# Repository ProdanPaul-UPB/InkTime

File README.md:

# InkTime — Open Source Smartwatch

InkTime is a low-power, open-source smartwatch built around the Nordic nRF52840 SoC and a 1.54" e-paper display. The goal was to design a device that can run for weeks on a single charge while still being useful as a daily wearable — no constant charging, no always-on backlight draining the battery.

This repo contains the full hardware design: schematic, PCB layout, manufacturing files, and the complete 3D assembly.

---

## Block Diagram

```
                        ┌─────────────────────────────────────────┐
                        │            nRF52840 (U1)                │
  USB-C (J4) ──► ESD ──►│ USB D+/D-          SPI ──────────────► │──► EPD Display (J1)
       │        (D3)    │                                         │    (Waveshare 1.54")
       │                │ I2C ──────────────────────────────────► │──► BMA423 IMU (IC3)
       ▼                │                   ├──────────────────► │──► MAX17048 Fuel Gauge (U3)
  BQ25180 (IC1) ───────►│ VBUS sense         └──────────────────► │──► DRV2605 Haptic (IC2)
  LiPo Charger          │                                         │
       │                │ GPIO ──────────────────────────────────►│──► SW_UP / SW_ENT / SW_DN
       ▼                │                                         │
  AKYGA LP502030        │ RF ────────────────────────────────────►│──► Matching Network
  3.7V / 250mAh         │                                         │    └──► ANT1 (2.4GHz)
       │                │ SWD ───────────────────────────────────►│──► TC2030-IDC (J2)
       ▼                └─────────────────────────────────────────┘
  RT6160A (IC9)
  DC-DC → 3.3V ──────────────────────────────────────────────────► All 3.3V rails
```

---

## Bill of Materials

| Ref | Component | Value / Part | Package | Datasheet | JLC Parts |
|-----|-----------|--------------|---------|-----------|-----------|
| U1 | Nordic nRF52840 | nRF52840-QIAA | QFN-73 | [Datasheet](https://infocenter.nordicsemi.com/pdf/nRF52840_PS_v1.7.pdf) | [JLC](https://jlcpcb.com/partdetail/NordicSemiconductor-nRF52840QIAA/C190794) |
| IC1 | TI BQ25180 | LiPo Charger | DSBGA-9 | [Datasheet](https://www.ti.com/lit/ds/symlink/bq25180.pdf) | [JLC](https://jlcpcb.com/parts/componentSearch?searchTxt=BQ25180) |
| IC9 | RT6160A | DC-DC Buck 3.3V | WSON-6 | [Datasheet](https://www.richtek.com/assets/product_file/RT6160A/DS6160A-00.pdf) | [JLC](https://jlcpcb.com/parts/componentSearch?searchTxt=RT6160A) |
| U3 | MAX17048G+T10 | Fuel Gauge | SOT-23-6 | [Datasheet](https://www.analog.com/media/en/technical-documentation/data-sheets/MAX17048-MAX17049.pdf) | [JLC](https://jlcpcb.com/parts/componentSearch?searchTxt=MAX17048) |
| IC3 | BMA423 | Accelerometer | LGA-12 | [Datasheet](https://www.bosch-sensortec.com/media/boschsensortec/downloads/datasheets/bst-bma423-ds000.pdf) | [JLC](https://jlcpcb.com/parts/componentSearch?searchTxt=BMA423) |
| IC2 | DRV2605YZFR | Haptic Driver | DSBGA-12 | [Datasheet](https://www.ti.com/lit/ds/symlink/drv2605.pdf) | [JLC](https://jlcpcb.com/parts/componentSearch?searchTxt=DRV2605) |
| D3 | USBLC6-2SC6Y | USB ESD | SOT-363 | [Datasheet](https://www.st.com/resource/en/datasheet/usblc6-2.pdf) | [JLC](https://jlcpcb.com/parts/componentSearch?searchTxt=USBLC6-2SC6Y) |
| J4 | KH-TYPE-C-16P | USB-C Receptacle | SMD | — | [JLC](https://jlcpcb.com/parts/componentSearch?searchTxt=TYPE-C-16P) |
| J1 | Molex 503480-2400 | 24-pin FPC | SMD | [Datasheet](https://www.molex.com/en-us/products/part-detail/503480-2400) | [JLC](https://jlcpcb.com/parts/componentSearch?searchTxt=503480-2400) |
| J2 | TC2030-IDC | SWD Connector | THT | [Datasheet](https://www.tag-connect.com/product/tc2030-idc-nl) | — |
| ANT1 | 2450AT18B100E | 2.4GHz Antenna | SMD | [Datasheet](https://www.johansontechnology.com/datasheets/2450AT18B100E/2450AT18B100E.pdf) | [JLC](https://jlcpcb.com/parts/componentSearch?searchTxt=2450AT18B100E) |
| X1 | 32MHz Crystal | HFXO | SMD | — | [JLC](https://jlcpcb.com/parts/componentSearch?searchTxt=32MHz+crystal) |
| X2 | 32.768kHz Crystal | LFXO | SMD | — | [JLC](https://jlcpcb.com/parts/componentSearch?searchTxt=32.768kHz+crystal) |
| SW1-3 | EVP-AKE31A | Tactile Button | SMD | [Datasheet](https://industrial.panasonic.com/cdbs/www-data/pdf/ATV0000/ATV0000CE5.pdf) | [JLC](https://jlcpcb.com/parts/componentSearch?searchTxt=EVP-AKE31A) |
| — | AKYGA LP502030 | 3.7V / 250mAh LiPo | — | [Datasheet](https://www.tme.eu/Document/b9e12bf26ad0ba929a22ab5d58f022cd/AKY0106.pdf) | External |
| — | Waveshare WSH-12561 | 1.54" EPD Display | FPC-24 | [Datasheet](https://www.tme.eu/Document/0ca57a8ffbcd57b5bca53252eb9d6ec3/WSH-12561.pdf) | External |
| — | DFRobot FIT0774 | Vibration Motor | Coin 10×2.7mm | [Product page](https://www.tme.eu/ro/details/df-fit0774/motoare-dc/dfrobot/fit0774/) | External |
| Q3 | DMG2305UX | P-MOSFET | SOT-523 | [Datasheet](https://www.diodes.com/assets/Datasheets/DMG2305UX.pdf) | [JLC](https://jlcpcb.com/parts/componentSearch?searchTxt=DMG2305UX) |
| Q4 | SI1308EDL | N-MOSFET | SC-70 | [Datasheet](https://www.vishay.com/docs/73217/si1308edl.pdf) | [JLC](https://jlcpcb.com/parts/componentSearch?searchTxt=SI1308EDL) |
| L5 | 68µH Inductor | EPD Boost | 0402 | — | [JLC](https://jlcpcb.com/parts/componentSearch?searchTxt=68uH+0402) |
| L1 | 3.9nH Inductor | RF Matching | 0402 | — | [JLC](https://jlcpcb.com/parts/componentSearch?searchTxt=3.9nH+0402) |
| L2 | 15nH Inductor | RF Matching | 0402 | — | [JLC](https://jlcpcb.com/parts/componentSearch?searchTxt=15nH+0402) |
| L7 | 4.7µH Inductor | DC-DC Switching | 0402 | — | [JLC](https://jlcpcb.com/parts/componentSearch?searchTxt=4.7uH+0402) |
| R9 | 10kΩ | TS/MR Pull-down | 0201 | — | [JLC](https://jlcpcb.com/parts/componentSearch?searchTxt=10k+0201) |
| Various C | 100nF / 1µF / 10µF / 22µF | Decoupling | 0201 / 0402 | — | [JLC](https://jlcpcb.com/parts/componentSearch?searchTxt=100nF+0201) |

---

## Hardware Description

### Power Path

Power enters through the USB-C connector (J4). The BQ25180 charger (IC1) handles incoming VBUS and takes care of charging the LiPo battery safely — it supports up to 1A charge current with I²C-configurable parameters. The RT6160A (IC9) is a synchronous buck DC-DC converter that takes the battery voltage (3.0–4.2V) and steps it down to a clean 3.3V rail used by everything else on the board. The MAX17048 fuel gauge (U3) sits on the I²C bus and reports state of charge to the MCU so the watch can display battery percentage without the MCU having to do any ADC math itself.

The battery (AKYGA LP502030) is soldered directly to two test pads on the board rather than using a JST connector — this saves ~2mm of vertical height which matters a lot inside a watch case.

### Microcontroller

The nRF52840 (U1) is the brain of the device. It's a Cortex-M4F running at 64MHz with built-in Bluetooth 5.0 and a hardware USB controller. We used the QFN-73 package which has a 5×5mm exposed thermal pad underneath — there are thermal vias going through to the bottom GND plane to help with heat dissipation. The chip runs off the 3.3V rail and has 13 decoupling capacitors placed in a ring around its pads, as close to the power pins as the 2.54mm grid allows.

### Display Interface

The 1.54" e-paper display (Waveshare WSH-12561) connects through a 24-pin FPC connector (J1, Molex 503480-2400) on the left edge of the board. The EPD uses a 4-wire SPI interface plus three control lines (DC, RST, BUSY). The display only draws current during refresh — in static mode it consumes essentially nothing, which is the main reason e-paper was chosen for a watch that's supposed to last weeks.

Driving an EPD requires specific voltages that 3.3V alone can't provide. The EPD drive circuit uses a boost converter (Q4 N-MOSFET + L5 68µH inductor + D2 Schottky rectifier) to generate the higher voltages the display panel needs for VCOM and VDD. Q3 is a P-MOSFET power switch that the MCU uses to completely cut power to the display when it doesn't need it.

### Inertial Measurement Unit

The BMA423 (IC3) is a 6-axis IMU that handles step counting, activity recognition, and wrist-tilt detection (to wake the display when the user raises their wrist). It communicates over I²C and has its own interrupt output connected to a GPIO on the nRF52840 so it can wake the MCU from deep sleep without the MCU polling.

### Haptic Feedback

The DRV2605 (IC2) is a haptic driver that can drive both ERM (eccentric rotating mass) and LRA (linear resonant actuator) motors. It connects over I²C and has a library of pre-programmed waveforms built into its ROM, so the MCU just writes an effect number and the chip handles the timing. The FIT0774 vibration motor is a 10×2.7mm coin ERM motor that sits in the corner of the case behind the PCB.

### Bluetooth / RF

The nRF52840's built-in 2.4GHz radio connects to a chip antenna (Johanson 2450AT18B100E) through a pi-type matching network made of two series inductors (L1 3.9nH, L2 15nH) and two shunt capacitors (C3, C5 each 1pF). The antenna is placed at the edge of the PCB with a keepout zone below it — no copper planes or signal traces run under the antenna. Via stitching connects the top and bottom GND planes around the RF area to prevent ground loops from affecting the antenna's radiation pattern.

### USB and ESD Protection

The USBLC6-2SC6Y (D3) is a dual-channel TVS diode array placed between the USB-C connector and the nRF52840's USB pins. It clamps any ESD spikes from the connector before they can reach the MCU. The two CC pull-down resistors (5.1kΩ each) on CC1 and CC2 tell the USB host that this is a UFP (upstream facing port) device drawing up to 500mA.

### Debug Interface

The TC2030-IDC (J2) is a Tag-Connect 2×5 pogo-pin footprint for SWD debugging. It brings out SWDIO, SWDCLK, SWO, and RESET so a J-Link or similar debugger can program and debug the nRF52840 without needing a soldered header. Several test pads scattered around the board (labeled in silkscreen) expose the main power rails and I²C/SPI signals for probing during bring-up.

---

## nRF52840 Pin Mapping

| Pin | Signal | Connected To | Notes |
|-----|--------|-------------|-------|
| P0.06 | SDA | BMA423, MAX17048, DRV2605, BQ25180 | Shared I²C data |
| P0.08 | SCL | BMA423, MAX17048, DRV2605, BQ25180 | Shared I²C clock |
| P0.11 | MOSI | EPD Display (J1) | SPI data to display |
| P0.12 | MISO | EPD Display (J1) | SPI data from display |
| P0.13 | SCK | EPD Display (J1) | SPI clock |
| P0.14 | CS_EPD | EPD Display (J1) | SPI chip select |
| P0.15 | DC_EPD | EPD Display (J1) | Data/Command select |
| P0.16 | RST_EPD | EPD Display (J1) | Display reset |
| P0.17 | BUSY_EPD | EPD Display (J1) | Display busy indicator |
| P0.02 | SW_UP | SW1 (Up button) | Active low, internal pull-up |
| P0.03 | SW_ENT | SW2 (Enter button) | Active low, internal pull-up |
| P0.04 | SW_DN | SW3 (Down button) | Active low, internal pull-up |
| P0.29 | INT_IMU | BMA423 (IC3) | Interrupt from IMU |
| P0.30 | EN_EPD | Q3 gate | EPD power switch enable |
| P0.31 | EN_HAP | DRV2605 IN/TRIG | Haptic trigger signal |
| P0.20 | D+ | USBLC6 → USB-C | USB data positive |
| P0.22 | D− | USBLC6 → USB-C | USB data negative |
| SWDIO | SWDIO | TC2030-IDC (J2) | SWD debug interface |
| SWDCLK | SWDCLK | TC2030-IDC (J2) | SWD debug clock |
| P0.18 | RESET | TC2030-IDC (J2) | Hardware reset |
| XC1/XC2 | HFXO | X1 (32MHz) | High-frequency crystal oscillator |
| XL1/XL2 | LFXO | X2 (32.768kHz) | Low-frequency crystal for RTC |

The I²C bus is shared between four ICs — the BMA423, MAX17048, DRV2605, and BQ25180. Each has a different I²C address so there are no conflicts. SCL runs at 400kHz (fast mode).

---

## Power Consumption (estimated)

| Mode | Current draw |
|------|-------------|
| Deep sleep (display static, BLE off) | ~10–15 µA |
| Active (BLE advertising, IMU polling) | ~3–5 mA |
| Display refresh (EPD update) | ~20–30 mA for ~2s |
| USB charging | up to 250mA (BQ25180 configured) |

With the 250mAh battery and an estimated average current of ~0.5mA (mostly in deep sleep, occasional display updates and BLE), the target runtime is around 3–4 weeks between charges.

---

## PCB Details

- **Board dimensions:** 45.72mm × 34.29mm
- **Layers:** 2 (Top + Bottom)
- **Thickness:** 1.0mm
- **Surface finish:** HASL or ENIG
- **Min trace width:** 0.15mm (signals), 0.3mm (power)
- **Via drill:** 0.3mm min
- **GND planes:** Both TOP and BOTTOM layers, connected via stitching vias
- **Stackup:** Signal + GND pour (TOP) / GND pour + Signal (BOTTOM)
- **Antenna keepout:** No copper or signals under ANT1

All components are on the TOP layer only.

---

## Known Issues and Design Decisions

- **Board outline clearance errors:** The three tactile buttons (SW1–SW3) and the USB-C connector are intentionally positioned so they protrude into the board edge clearance zone. This is by design — they need to align with cutouts in the physical case and this placement was confirmed in the reference `.fbrd` layout from the course. These DRC errors are accepted and documented here.

- **Drill size errors:** Some via drill sizes fall slightly below the JLCPCB minimum due to the dense BGA escape routing under U1. These were the smallest vias needed to escape the MCU pads while still leaving clearance for adjacent traces. A PCB house that supports 0.2mm drills (like PCBWay) can manufacture these without issue. For JLCPCB specifically, these can be bumped to 0.3mm at the cost of routing one or two signals to alternate paths.

- **Battery connection:** The battery is soldered directly to TP_VBAT and TP_GND test pads instead of using the JST connector. This was intentional to reduce the height of the assembly so it fits inside the 1.0mm-thick PCB + battery stack constraint of the inktime_case enclosure.

- **EPD drive circuit:** The boost converter was designed around the voltage requirements in the WSH-12561 datasheet. The VCOM voltage is set via SJ1 — the solder jumper selects between direct GND and a resistor-divided reference, allowing adjustment during bring-up if the display contrast isn't right with the default value.

---

## Repository Structure

```
Hardware/
├── inktime.sch          — Schematic (Fusion 360 / EAGLE format)
├── inktime.brd          — PCB board file
└── inktime_schematic.pdf
Manufacturing/
├── gerbers.zip
├── inktime.bom
└── inktime.cpl
Mechanical/
├── inktime_assembly_exploded.step
└── inktime_complete.f3z
Images/
└── (PCB renders and assembly photos)
LICENSE
README.md
```

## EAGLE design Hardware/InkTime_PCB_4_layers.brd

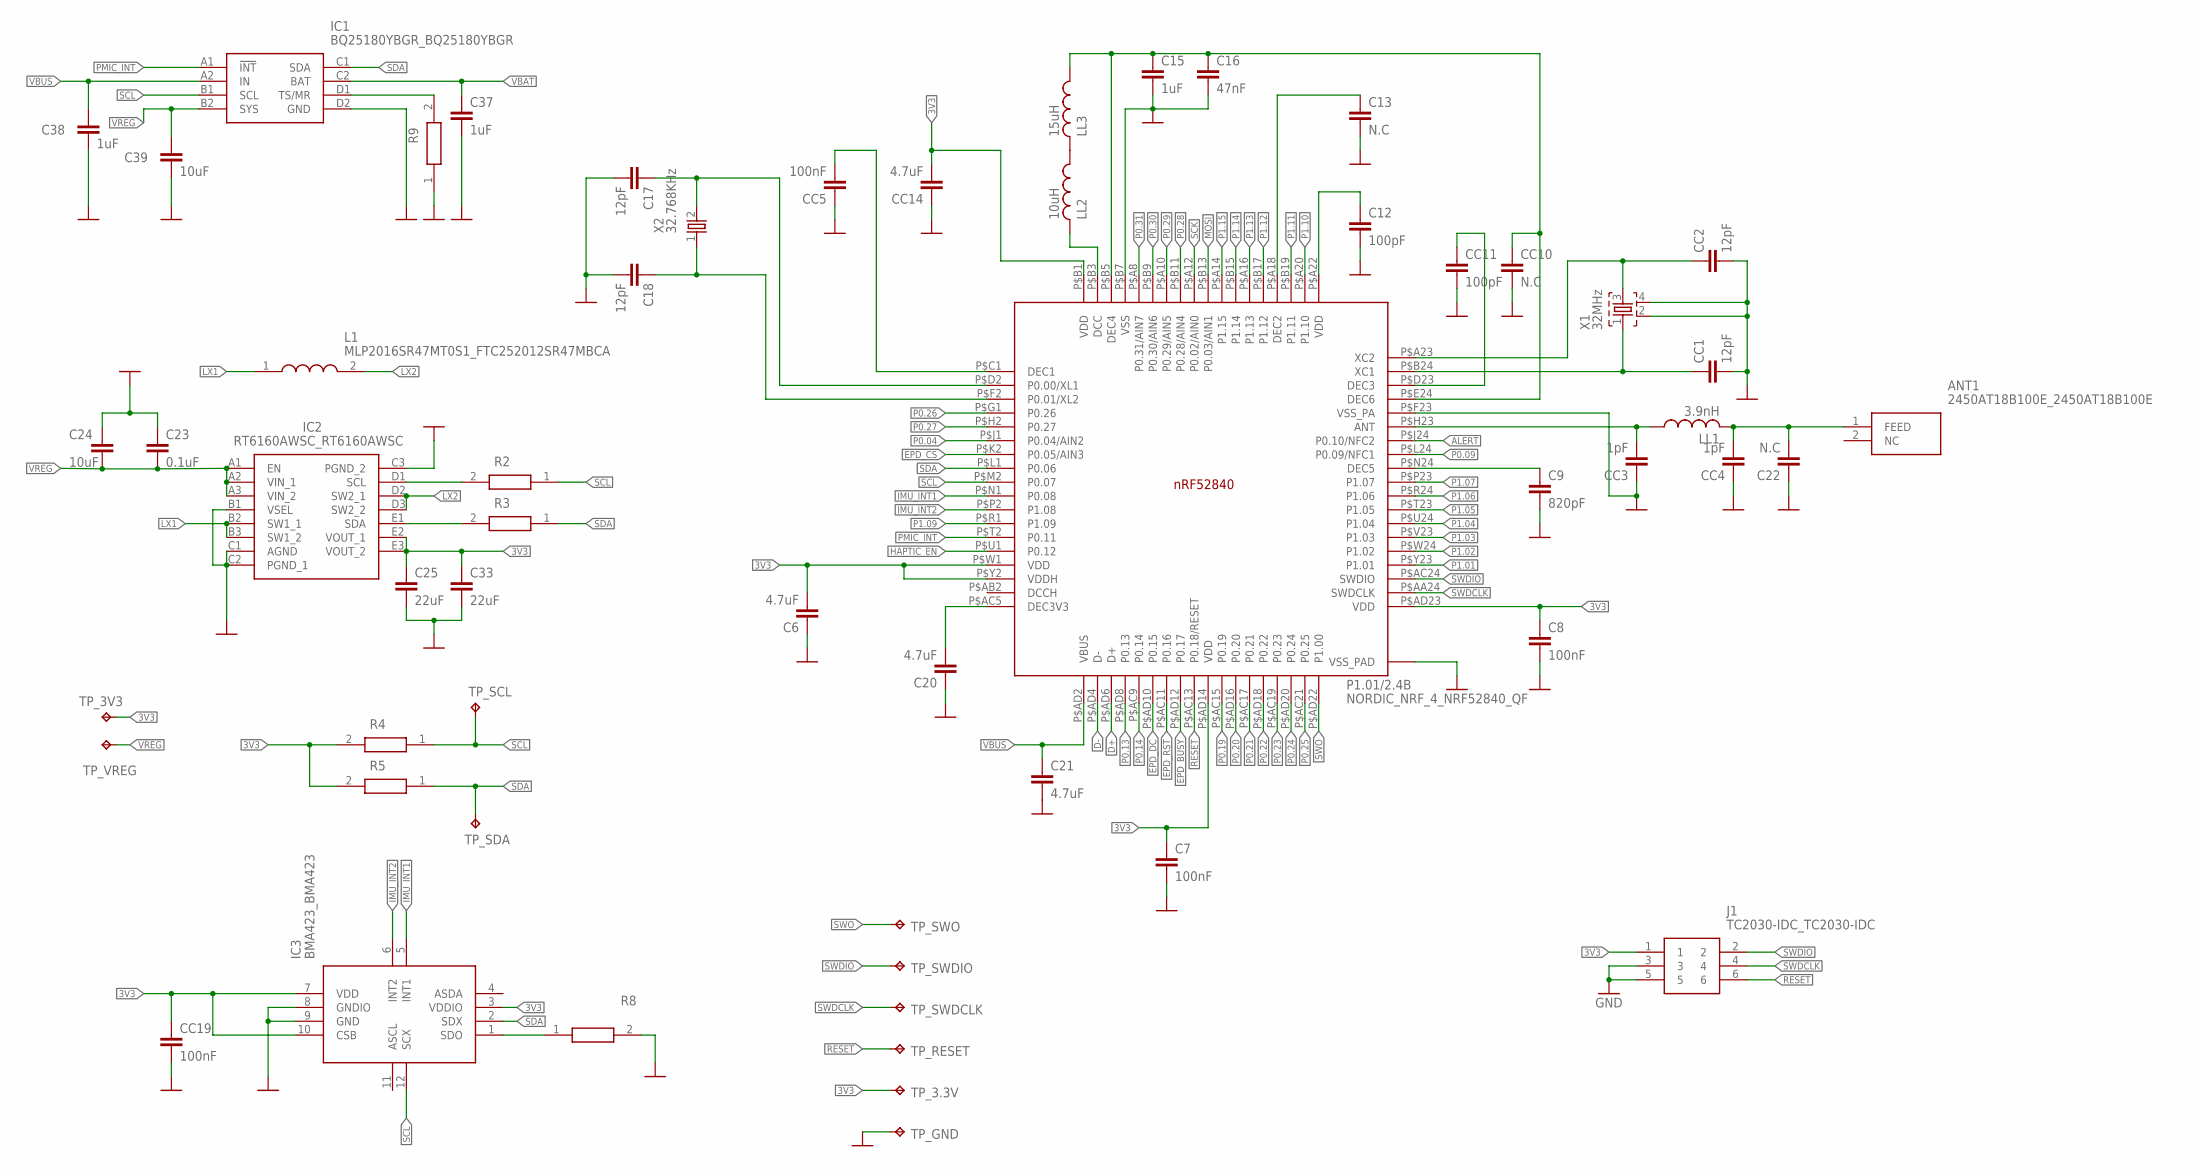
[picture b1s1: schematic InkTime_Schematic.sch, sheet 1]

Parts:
ANT1: 2450AT18B100E_2450AT18B100E; 2450AT18B100E_ANTC3216X140N
C6, C20, C21: 4.7uF; NORDIC_NRF_3_RESC0402_M
C7, C8: 100nF; NORDIC_NRF_3_RESC0402_M
C9: 820pF; NORDIC_NRF_3_RESC0402_M
C12: 100pF; NORDIC_NRF_3_RESC0402_M
C13, C22: N.C; NORDIC_NRF_3_RESC0402_M
C15, C37, C38: 1uF; NORDIC_NRF_3_RESC0402_M
C16: 47nF; NORDIC_NRF_3_RESC0402_M
C17, C18: 12pF; NORDIC_NRF_3_RESC0402_M
C23: 0.1uF; NORDIC_NRF_3_RESC0402_M
C24, C39: 10uF; NORDIC_NRF_3_RESC0402_M
C25, C33: 22uF; NORDIC_NRF_3_RESC0402_M
CC1, CC2: 12pF; NORDIC_NRF_3_RESC0402_M
CC3, CC4: 1pF; NORDIC_NRF_3_RESC0402_M
CC5, CC19: 100nF; NORDIC_NRF_3_RESC0402_M
CC10: N.C; NORDIC_NRF_3_RESC0402_M
CC11: 100pF; NORDIC_NRF_3_RESC0402_M
CC14: 4.7uF; NORDIC_NRF_3_RESC0402_M
IC1: BQ25180YBGR_BQ25180YBGR; BQ25180YBGR_BGA8C40P2X4_100X155X50
IC2: RT6160AWSC_RT6160AWSC; RT6160AWSC_BGA15C40P3X5_140X230X60
IC3: BMA423_BMA423
J1: TC2030-IDC_TC2030-IDC; TC2030-IDC_TC2030IDC
L1: MLP2016SR47MT0S1_FTC252012SR47MBCA; MLP2016SR47MT0S1_INDC2016X100N
LL1: 3.9nH; NORDIC_NRF_2_RESC0402_M
LL2: 10uH; NORDIC_NRF_2_RESC0402_M
LL3: 15uH; NORDIC_NRF_2_RESC0402_M
P1.01/2.4B: NORDIC_NRF_4_NRF52840_QF; NORDIC_NRF_4_AQFN50P700X700X85_HS-74N
R2, R3, R4, R5, R8: CPF0201D7K68C1_CPF0201D7K68C1; CPF0201D7K68C1_0201
R9: 10K; CPF0201D7K68C1_0201
TP_3.3V, TP_3V3: HECTOR_WATCH_1_TPTP20R; HECTOR_WATCH_1_TP20R
TP_GND: HECTOR_WATCH_1_TPTP20R; HECTOR_WATCH_1_TP20R
TP_RESET: HECTOR_WATCH_1_TPTP20R; HECTOR_WATCH_1_TP20R
TP_SCL: HECTOR_WATCH_1_TPTP20R; HECTOR_WATCH_1_TP20R
TP_SDA: HECTOR_WATCH_1_TPTP20R; HECTOR_WATCH_1_TP20R
TP_SWDCLK: HECTOR_WATCH_1_TPTP20R; HECTOR_WATCH_1_TP20R
TP_SWDIO: HECTOR_WATCH_1_TPTP20R; HECTOR_WATCH_1_TP20R
TP_SWO: HECTOR_WATCH_1_TPTP20R; HECTOR_WATCH_1_TP20R
TP_VREG: HECTOR_WATCH_1_TPTP20R; HECTOR_WATCH_1_TP20R
X1: 32MHz; NORDIC_NRF_BT-XTAL_2016_N
X2: 32.768KHz; NORDIC_NRF_1_XTAL_3215_N

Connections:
ALERT: P1.01/2.4B.P$J24 (P0.10/NFC2); also elsewhere on the board
D+: P1.01/2.4B.P$AD6 (D+); also elsewhere on the board
D-: P1.01/2.4B.P$AD4 (D-); also elsewhere on the board
EPD_BUSY: P1.01/2.4B.P$AD12 (P0.17); also elsewhere on the board
EPD_CS: P1.01/2.4B.P$K2 (P0.05/AIN3); also elsewhere on the board
EPD_DC: P1.01/2.4B.P$AD10 (P0.15); also elsewhere on the board
EPD_RST: P1.01/2.4B.P$AC11 (P0.16); also elsewhere on the board
GND: C6.1, C7.2, C8.2, C9.2, C12.2, C13.2, C15.2, C16.2, C17.2, C18.2, C20.1, C21.2, C22.1, C23.1, C24.1, C25.2, C33.2, C37.2, C38.2, C39.2, CC1.2, CC2.2, CC3.1, CC4.1, CC5.1, CC10.2, CC11.2, CC14.1, CC19.2, IC1.D2 (GND), IC2.B1 (VSEL), IC2.C1 (AGND), IC2.C2 (PGND_1), IC2.C3 (PGND_2), IC3.8 (GNDIO), IC3.9 (GND), J1.3, J1.5, P1.01/2.4B.P$74 (VSS_PAD), P1.01/2.4B.P$75 (VSS_PAD), P1.01/2.4B.P$76 (VSS_PAD), P1.01/2.4B.P$77 (VSS_PAD), P1.01/2.4B.P$78 (VSS_PAD), P1.01/2.4B.P$79 (VSS_PAD), P1.01/2.4B.P$80 (VSS_PAD), P1.01/2.4B.P$81 (VSS_PAD), P1.01/2.4B.P$82 (VSS_PAD), P1.01/2.4B.P$83 (VSS_PAD), P1.01/2.4B.P$84 (VSS_PAD), P1.01/2.4B.P$85 (VSS_PAD), P1.01/2.4B.P$86 (VSS_PAD), P1.01/2.4B.P$87 (VSS_PAD), P1.01/2.4B.P$88 (VSS_PAD), P1.01/2.4B.P$89 (VSS_PAD), P1.01/2.4B.P$90 (VSS_PAD), P1.01/2.4B.P$B7 (VSS), P1.01/2.4B.P$F23 (VSS_PA), R8.2, R9.1, TP_GND.TP, X1.2, X1.4; also elsewhere on the board
HAPTIC_EN: P1.01/2.4B.P$U1 (P0.12); also elsewhere on the board
IMU_INT1: IC3.5 (INT1), P1.01/2.4B.P$N1 (P0.08)
IMU_INT2: IC3.6 (INT2), P1.01/2.4B.P$P2 (P1.08)
LX1: IC2.B2 (SW1_1), IC2.B3 (SW1_2), L1.1
LX2: IC2.D2 (SW2_1), IC2.D3 (SW2_2), L1.2
MOSI: P1.01/2.4B.P$B13 (P0.03/AIN1); also elsewhere on the board
unnamed: IC1.D1 (TS/MR), R9.2
unnamed: C9.1, P1.01/2.4B.P$N24 (DEC5)
unnamed: CC3.2, LL1.1, P1.01/2.4B.P$H23 (ANT)
unnamed: IC2.D1 (SCL), R2.2
unnamed: IC2.E1 (SDA), R3.2
unnamed: C20.2, P1.01/2.4B.P$AC5 (DEC3V3)
unnamed 24: ANT1.1 (FEED), C22.2, CC4.2, LL1.2; also elsewhere on the board
unnamed: CC1.1, P1.01/2.4B.P$B24 (XC1), X1.1
unnamed: CC2.1, P1.01/2.4B.P$A23 (XC2), X1.3
unnamed: CC11.1, P1.01/2.4B.P$D23 (DEC3)
unnamed: C18.1, P1.01/2.4B.P$F2 (P0.01/XL2), X2.1
unnamed: C12.1, P1.01/2.4B.P$A22 (VDD)
unnamed: C13.1, P1.01/2.4B.P$A18 (DEC2)
unnamed: LL2.1, LL3.2
unnamed: LL2.2, P1.01/2.4B.P$B3 (DCC)
unnamed: C15.1, C16.1, CC10.1, LL3.1, P1.01/2.4B.P$B5 (DEC4), P1.01/2.4B.P$E24 (DEC6)
unnamed: C17.1, P1.01/2.4B.P$D2 (P0.00/XL1), X2.2
unnamed: IC3.1 (SDO), R8.1
unnamed: CC5.2, P1.01/2.4B.P$C1 (DEC1)
P0.04: P1.01/2.4B.P$J1 (P0.04/AIN2)
P0.09: P1.01/2.4B.P$L24 (P0.09/NFC1)
P0.13: P1.01/2.4B.P$AD8 (P0.13); also elsewhere on the board
P0.14: P1.01/2.4B.P$AC9 (P0.14); also elsewhere on the board
P0.19: P1.01/2.4B.P$AC15 (P0.19)
P0.20: P1.01/2.4B.P$AD16 (P0.20)
P0.21: P1.01/2.4B.P$AC17 (P0.21)
P0.22: P1.01/2.4B.P$AD18 (P0.22)
P0.23: P1.01/2.4B.P$AC19 (P0.23)
P0.24: P1.01/2.4B.P$AD20 (P0.24)
P0.25: P1.01/2.4B.P$AC21 (P0.25)
P0.26: P1.01/2.4B.P$G1 (P0.26)
P0.27: P1.01/2.4B.P$H2 (P0.27)
P0.28: P1.01/2.4B.P$B11 (P0.28/AIN4)
P0.29: P1.01/2.4B.P$A10 (P0.29/AIN5)
P0.30: P1.01/2.4B.P$B9 (P0.30/AIN6)
P0.31: P1.01/2.4B.P$A8 (P0.31/AIN7)
P1.01: P1.01/2.4B.P$Y23 (P1.01); also elsewhere on the board
P1.02: P1.01/2.4B.P$W24 (P1.02); also elsewhere on the board
P1.03: P1.01/2.4B.P$V23 (P1.03)
P1.04: P1.01/2.4B.P$U24 (P1.04)
P1.05: P1.01/2.4B.P$T23 (P1.05)
P1.06: P1.01/2.4B.P$R24 (P1.06)
P1.07: P1.01/2.4B.P$P23 (P1.07)
P1.09: P1.01/2.4B.P$R1 (P1.09)
P1.10: P1.01/2.4B.P$A20 (P1.10)
P1.11: P1.01/2.4B.P$B19 (P1.11)
P1.12: P1.01/2.4B.P$B17 (P1.12)
P1.13: P1.01/2.4B.P$A16 (P1.13)
P1.14: P1.01/2.4B.P$B15 (P1.14)
P1.15: P1.01/2.4B.P$A14 (P1.15)
PMIC_INT: IC1.A1 (!INT), P1.01/2.4B.P$T2 (P0.11)
RESET: J1.6, P1.01/2.4B.P$AC13 (P0.18/RESET), TP_RESET.TP; also elsewhere on the board
SCK: P1.01/2.4B.P$A12 (P0.02/AIN0); also elsewhere on the board
SWDCLK: J1.4, P1.01/2.4B.P$AA24 (SWDCLK), TP_SWDCLK.TP; also elsewhere on the board
SWDIO: J1.2, P1.01/2.4B.P$AC24 (SWDIO), TP_SWDIO.TP; also elsewhere on the board
SWO: P1.01/2.4B.P$AD22 (P1.00), TP_SWO.TP; also elsewhere on the board
VREG: C23.2, C24.2, C39.1, IC1.B2 (SYS), IC2.A1 (EN), IC2.A2 (VIN_1), IC2.A3 (VIN_2), TP_VREG.TP

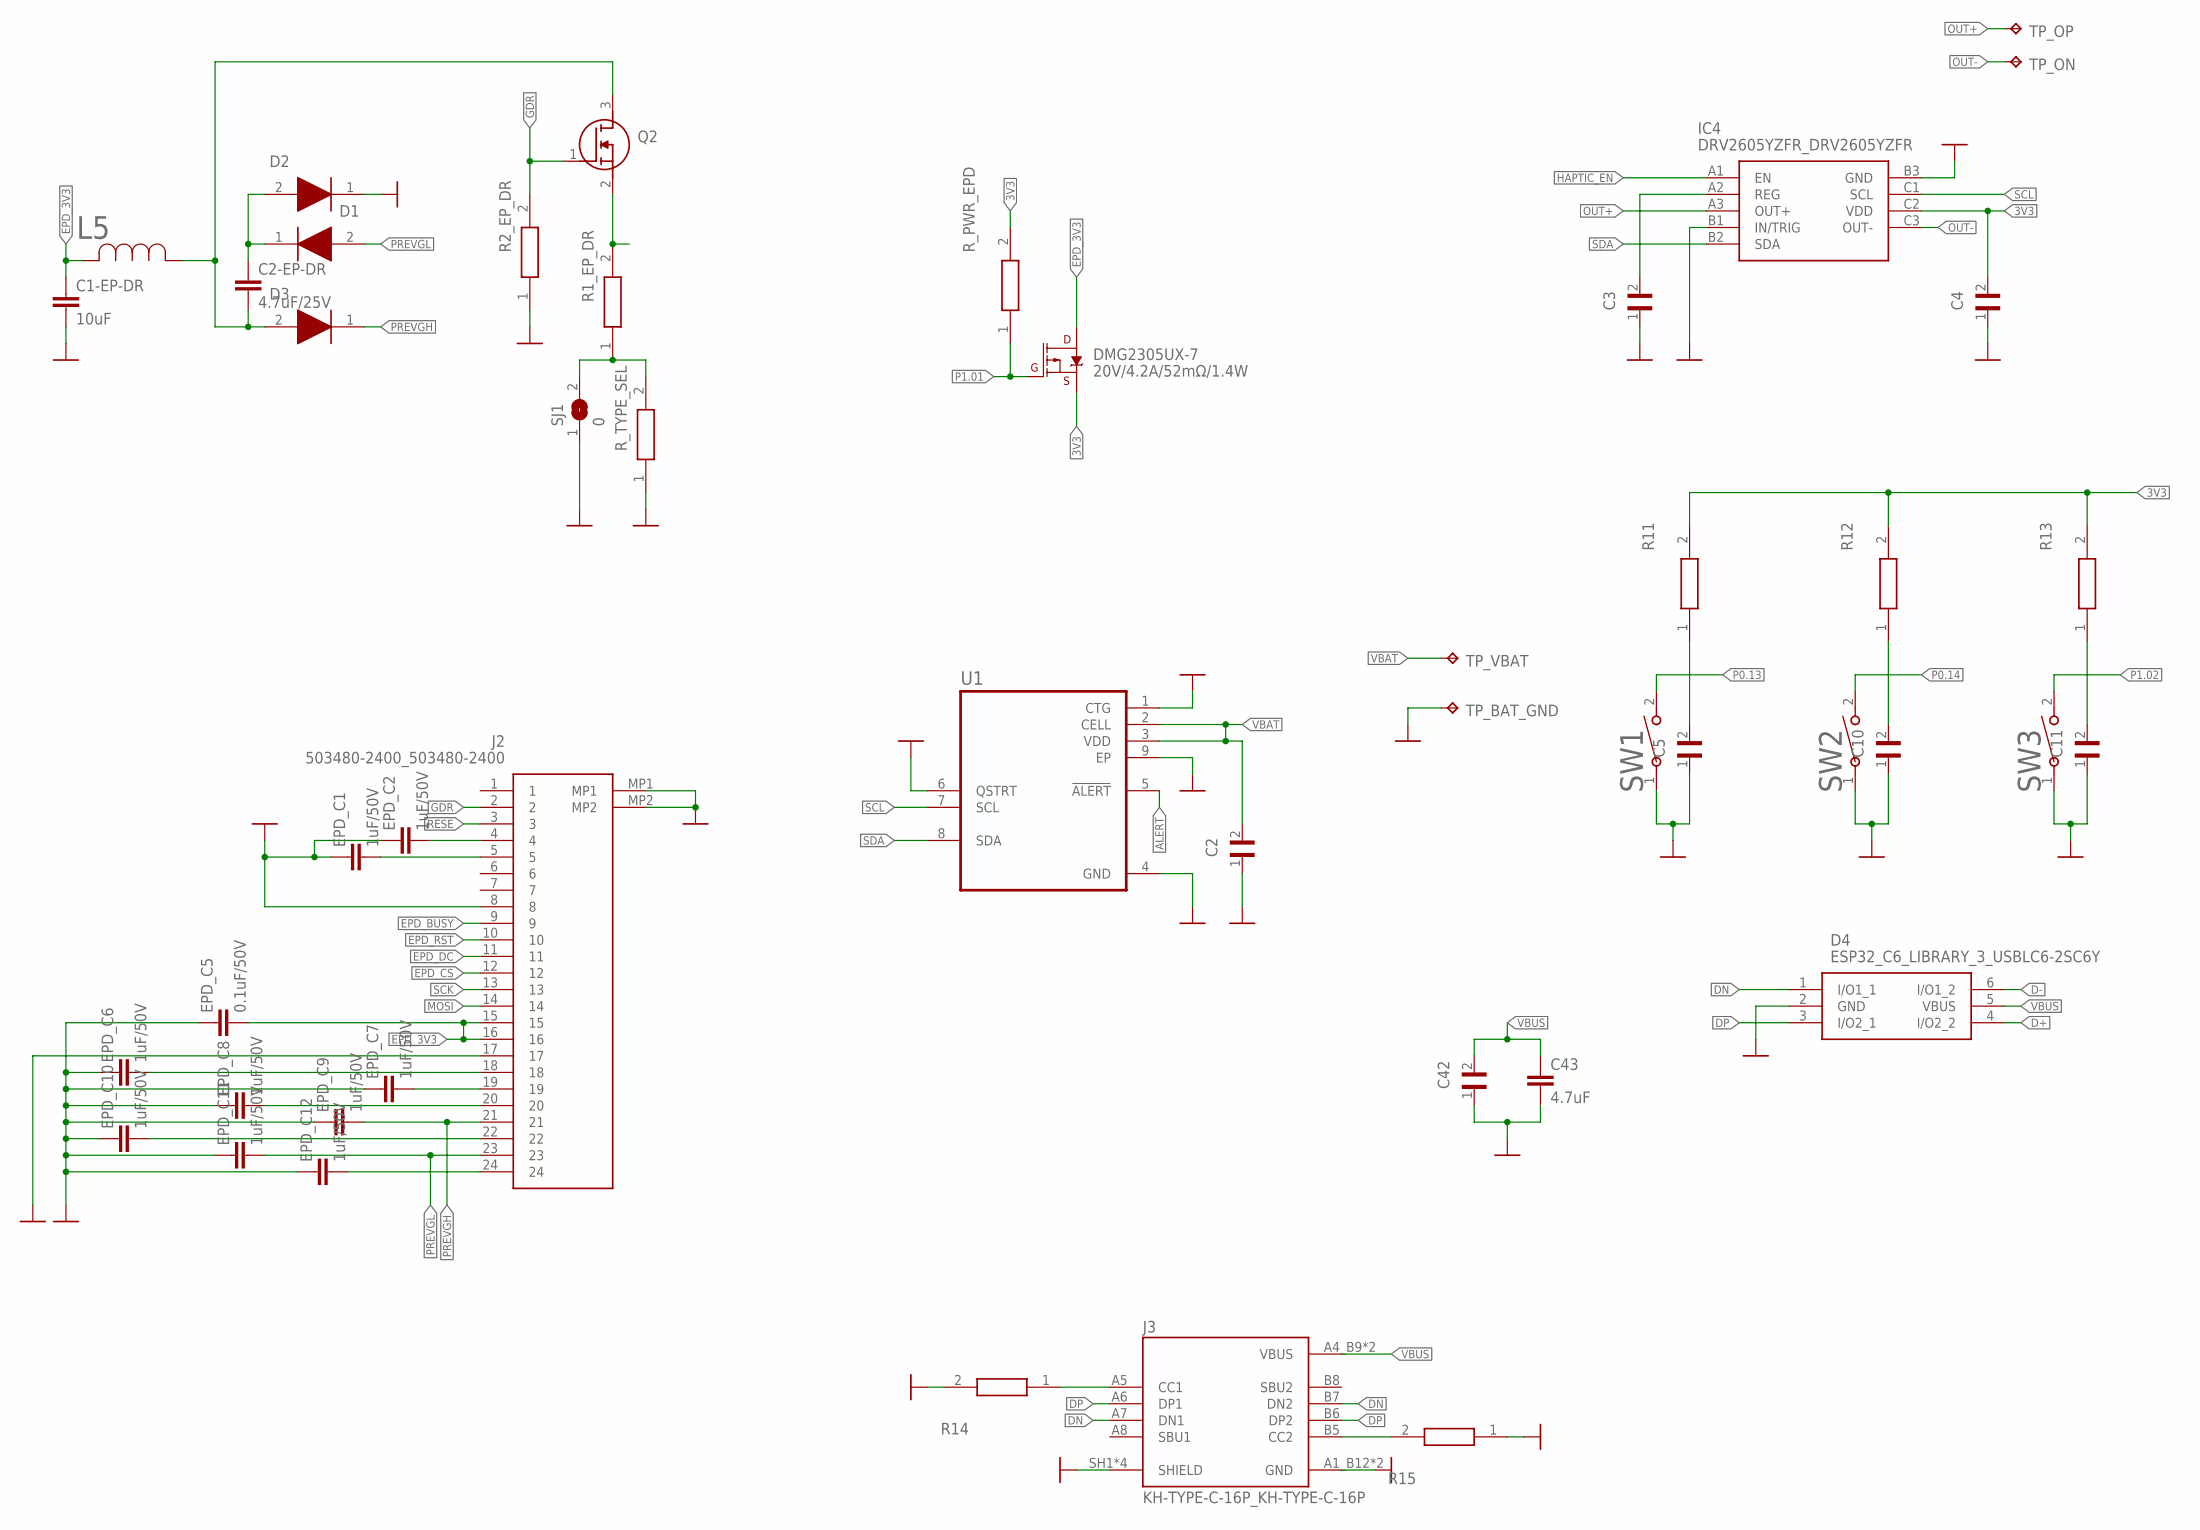
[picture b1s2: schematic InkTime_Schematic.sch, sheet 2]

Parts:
C1-EP-DR: 10uF; NORDIC_NRF_3_RESC0402_M
C2, C5, C10, C11, C42: GRM011R60J152KE01L_1_GRM011R60J152KE01L; GRM011R60J152KE01L_1_0201
C2-EP-DR: 4.7uF/25V; ESP32_C6_LIBRARY_1_ESP32_WROVER_EAGLE-LTSPICE_C0402
C3: 1uF; GRM011R60J152KE01L_1_0201
C4: 0.1uF; GRM011R60J152KE01L_1_0201
C43: 4.7uF; NORDIC_NRF_3_RESC0402_M
D1, D2, D3: ESP32_C6_LIBRARY_5_MBR0530; ESP32_C6_LIBRARY_5_SOD3716X135N
D4: ESP32_C6_LIBRARY_3_USBLC6-2SC6Y; ESP32_C6_LIBRARY_3_SOT95P280X145-6N
DMG2305UX-7: 20V/4.2A/52mΩ/1.4W; ESP32_C6_LIBRARY_4_ESP32_C6_LIBRARY_4_ESP32_C6_LIBRARY_4_ES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
EPD_C1, EPD_C2, EPD_C6, EPD_C7, EPD_C8, EPD_C9, EPD_C10, EPD_C11, EPD_C12: 1uF/50V; NORDIC_NRF_3_RESC0402_M
EPD_C5: 0.1uF/50V; NORDIC_NRF_3_RESC0402_M
IC4: DRV2605YZFR_DRV2605YZFR; DRV2605YZFR_BGA9C50P3X3_144X144X62
J2: 503480-2400_503480-2400; 503480-2400_5034802400
J3: KH-TYPE-C-16P_KH-TYPE-C-16P; KH-TYPE-C-16P_KINGHELM_KH-TYPE-C-16P
L5: ESP32_C6_LIBRARY_2_744043680IND_4828-WE-TPC_WRE; ESP32_C6_LIBRARY_2_IND_4828-WE-TPC_WRE
Q2: ESP32_C6_LIBRARY_6_SI1308EDL-T1-GE3; ESP32_C6_LIBRARY_6_SOT65P210X110-3N
R1_EP_DR, R2_EP_DR, R11, R12, R13, R14, R15: CPF0201D7K68C1_CPF0201D7K68C1; CPF0201D7K68C1_0201
R_PWR_EPD: CPF0201D7K68C1_CPF0201D7K68C1; CPF0201D7K68C1_0201
R_TYPE_SEL: CPF0201D7K68C1_CPF0201D7K68C1; CPF0201D7K68C1_0201
SJ1: 0; ESP32_C6_LIBRARY_7_JUMPER_SJ
SW1, SW2, SW3: 2025-10-22_07-23-44_LIBRARY_EVP-AKE31ASW_EVP-AKE3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; 2025-10-22_07-23-44_LIBRARY_SW_EVP-AKE31A_PAN
TP_BAT_GND: HECTOR_WATCH_1_TPTP20R; HECTOR_WATCH_1_TP20R
TP_ON: HECTOR_WATCH_1_TPTP20R; HECTOR_WATCH_1_TP20R
TP_OP: HECTOR_WATCH_1_TPTP20R; HECTOR_WATCH_1_TP20R
TP_VBAT: HECTOR_WATCH_1_TPTP20R; HECTOR_WATCH_1_TP20R
U1: ESP32_C6_LIBRARY_MAX17048G+T10; ESP32_C6_LIBRARY_SON50P200X200X80-9N

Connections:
ALERT: U1.5 (!ALERT); also elsewhere on the board
D+: D4.4 (I/O2_2); also elsewhere on the board
D-: D4.6 (I/O1_2); also elsewhere on the board
DN: D4.1 (I/O1_1), J3.A7 (DN1), J3.B7 (DN2)
DP: D4.3 (I/O2_1), J3.A6 (DP1), J3.B6 (DP2)
EPD_3V3: C1-EP-DR.1, DMG2305UX-7.3 (D), EPD_C5.2, J2.15, J2.16, L5.2
EPD_BUSY: J2.9; also elsewhere on the board
EPD_CS: J2.12; also elsewhere on the board
EPD_DC: J2.11; also elsewhere on the board
EPD_RST: J2.10; also elsewhere on the board
GDR: J2.2, Q2.1 (G), R2_EP_DR.2
GND: C1-EP-DR.2, C2.1, C3.1, C4.1, C5.1, C10.1, C11.1, C42.1, C43.2, D2.1 (K), D4.2 (GND), EPD_C1.1, EPD_C2.1, EPD_C5.1, EPD_C6.1, EPD_C7.1, EPD_C8.1, EPD_C9.1, EPD_C10.1, EPD_C11.1, EPD_C12.1, IC4.B1 (IN/TRIG), IC4.B3 (GND), J2.8, J2.17, J2.MP1, J2.MP2, J3.A1_B12 (GND), J3.A12_B1 (GND), J3.SH1 (SHIELD), J3.SH2 (SHIELD), J3.SH3 (SHIELD), J3.SH4 (SHIELD), R2_EP_DR.1, R14.2, R15.1, R_TYPE_SEL.1, SJ1.1, SW1.1, SW2.1, SW3.1, TP_BAT_GND.TP, U1.1 (CTG), U1.4 (GND), U1.6 (QSTRT), U1.9 (EP); also elsewhere on the board
HAPTIC_EN: IC4.A1 (EN); also elsewhere on the board
MOSI: J2.14; also elsewhere on the board
unnamed: C2-EP-DR.1, D1.1 (K), D2.2 (A)
unnamed: Q2.2 (S), R1_EP_DR.2
unnamed: R1_EP_DR.1, R_TYPE_SEL.2, SJ1.2
unnamed: C2-EP-DR.2, D3.2 (A), L5.1, Q2.3 (D)
unnamed: EPD_C2.2, J2.4
unnamed: EPD_C1.2, J2.5
unnamed: J3.B5 (CC2), R15.2
unnamed: EPD_C7.2, J2.19
unnamed: C5.2, R11.1
unnamed: EPD_C12.2, J2.24
unnamed: EPD_C6.2, J2.18
unnamed: EPD_C8.2, J2.20
unnamed: C10.2, R12.1
unnamed: EPD_C10.2, J2.22
unnamed: C11.2, R13.1
unnamed: J3.A5 (CC1), R14.1
unnamed: C3.2, IC4.A2 (REG)
OUT+: IC4.A3 (OUT+), TP_OP.TP; also elsewhere on the board
OUT-: IC4.C3 (OUT-), TP_ON.TP; also elsewhere on the board
P0.13: SW1.2; also elsewhere on the board
P0.14: SW2.2; also elsewhere on the board
P1.01: DMG2305UX-7.1 (G), R_PWR_EPD.1; also elsewhere on the board
P1.02: SW3.2; also elsewhere on the board
PREVGH: D3.1 (K), EPD_C9.2, J2.21
PREVGL: D1.2 (A), EPD_C11.2, J2.23
RESE: J2.3
SCK: J2.13; also elsewhere on the board

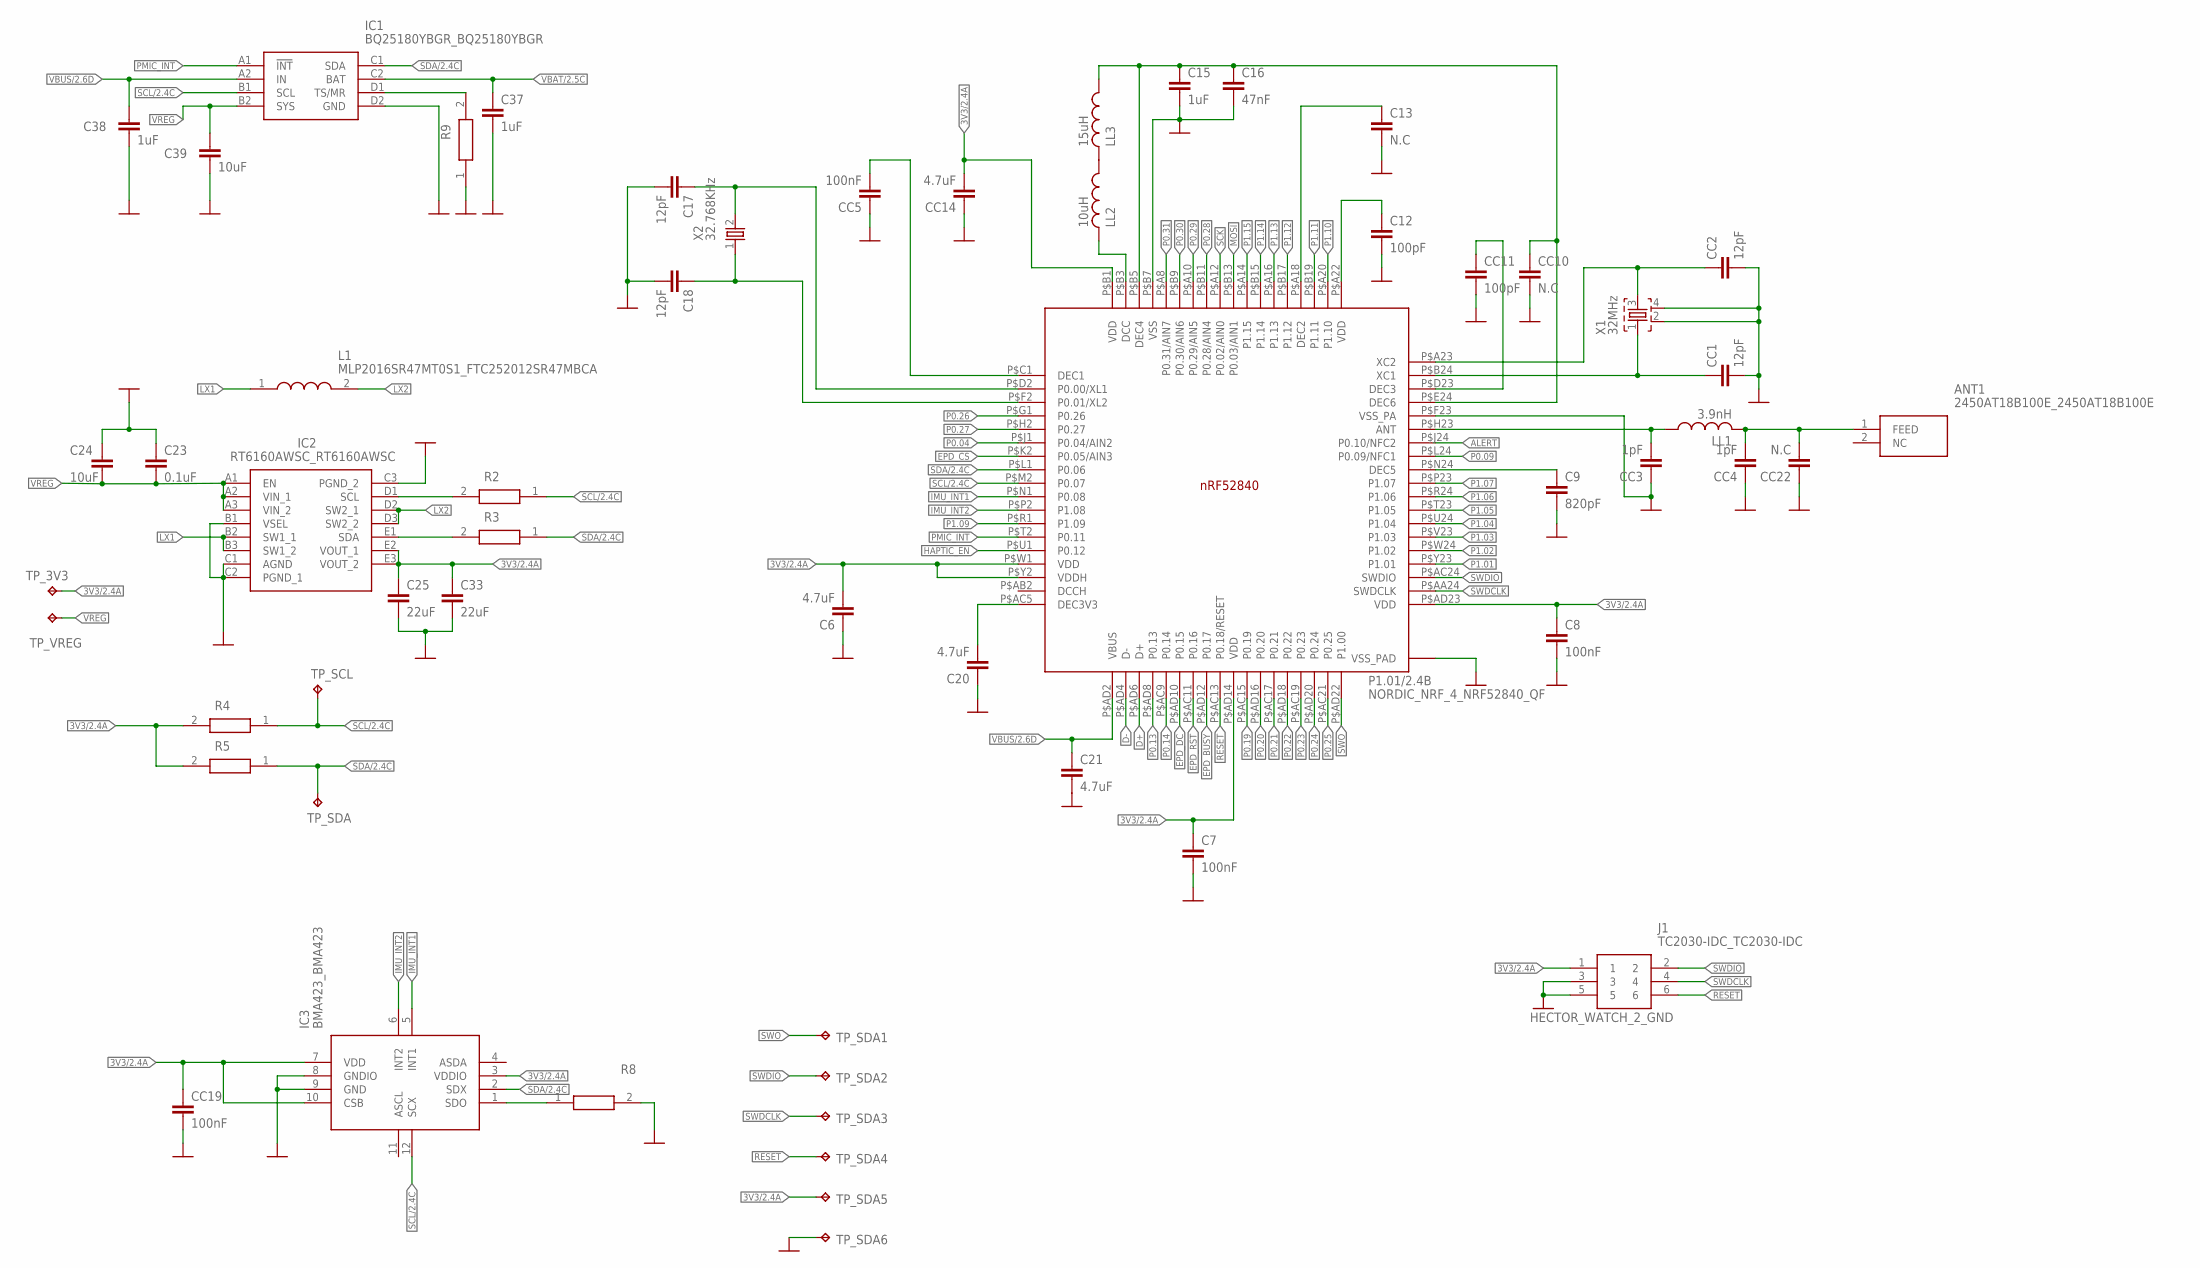
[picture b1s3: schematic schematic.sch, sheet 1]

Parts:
ANT1: 2450AT18B100E_2450AT18B100E; 2450AT18B100E_ANTC3216X140N
C6, C20, C21: 4.7uF; NORDIC_NRF_3_RESC0402_M
C7, C8: 100nF; NORDIC_NRF_3_RESC0402_M
C9: 820pF; NORDIC_NRF_3_RESC0402_M
C12: 100pF; NORDIC_NRF_3_RESC0402_M
C13: N.C; NORDIC_NRF_3_RESC0402_M
C15, C37, C38: 1uF; NORDIC_NRF_3_RESC0402_M
C16: 47nF; NORDIC_NRF_3_RESC0402_M
C17, C18: 12pF; NORDIC_NRF_3_RESC0402_M
C23: 0.1uF; NORDIC_NRF_3_RESC0402_M
C24, C39: 10uF; NORDIC_NRF_3_RESC0402_M
C25, C33: 22uF; NORDIC_NRF_3_RESC0402_M
CC1, CC2: 12pF; NORDIC_NRF_3_RESC0402_M
CC3, CC4: 1pF; NORDIC_NRF_3_RESC0402_M
CC5, CC19: 100nF; NORDIC_NRF_3_RESC0402_M
CC10, CC22: N.C; NORDIC_NRF_3_RESC0402_M
CC11: 100pF; NORDIC_NRF_3_RESC0402_M
CC14: 4.7uF; NORDIC_NRF_3_RESC0402_M
IC1: BQ25180YBGR_BQ25180YBGR; BQ25180YBGR_BGA8C40P2X4_100X155X50
IC2: RT6160AWSC_RT6160AWSC; RT6160AWSC_BGA15C40P3X5_140X230X60
IC3: BMA423_BMA423
J1: TC2030-IDC_TC2030-IDC; TC2030-IDC_TC2030IDC
L1: MLP2016SR47MT0S1_FTC252012SR47MBCA; MLP2016SR47MT0S1_INDC2016X100N
LL1: 3.9nH; NORDIC_NRF_2_RESC0402_M
LL2: 10uH; NORDIC_NRF_2_RESC0402_M
LL3: 15uH; NORDIC_NRF_2_RESC0402_M
P1.01/2.4B: NORDIC_NRF_4_NRF52840_QF; NORDIC_NRF_4_AQFN50P700X700X85_HS-74N
R2, R3, R4, R5, R8: CPF0201D7K68C1_CPF0201D7K68C1; CPF0201D7K68C1_0201
R9: 10K; CPF0201D7K68C1_0201
TP_3V3: HECTOR_WATCH_1_TPTP20R; HECTOR_WATCH_1_TP20R
TP_SCL: HECTOR_WATCH_1_TPTP20R; HECTOR_WATCH_1_TP20R
TP_SDA, TP_SDA1, TP_SDA2, TP_SDA3, TP_SDA4, TP_SDA5, TP_SDA6: HECTOR_WATCH_1_TPTP20R; HECTOR_WATCH_1_TP20R
TP_VREG: HECTOR_WATCH_1_TPTP20R; HECTOR_WATCH_1_TP20R
X1: 32MHz; NORDIC_NRF_BT-XTAL_2016_N
X2: 32.768KHz; NORDIC_NRF_1_XTAL_3215_N

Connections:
ALERT: P1.01/2.4B.P$J24 (P0.10/NFC2); also elsewhere on the board
D+: P1.01/2.4B.P$AD6 (D+); also elsewhere on the board
D-: P1.01/2.4B.P$AD4 (D-); also elsewhere on the board
EPD_BUSY: P1.01/2.4B.P$AD12 (P0.17); also elsewhere on the board
EPD_CS: P1.01/2.4B.P$K2 (P0.05/AIN3); also elsewhere on the board
EPD_DC: P1.01/2.4B.P$AD10 (P0.15); also elsewhere on the board
EPD_RST: P1.01/2.4B.P$AC11 (P0.16); also elsewhere on the board
GND: C6.1, C7.2, C8.2, C9.2, C12.2, C13.2, C15.2, C16.2, C17.2, C18.2, C20.1, C21.2, C23.1, C24.1, C25.2, C33.2, C37.2, C38.2, C39.2, CC1.2, CC2.2, CC3.1, CC4.1, CC5.1, CC10.2, CC11.2, CC14.1, CC19.2, CC22.1, IC1.D2 (GND), IC2.B1 (VSEL), IC2.C1 (AGND), IC2.C2 (PGND_1), IC2.C3 (PGND_2), IC3.8 (GNDIO), IC3.9 (GND), J1.3, J1.5, P1.01/2.4B.P$74 (VSS_PAD), P1.01/2.4B.P$75 (VSS_PAD), P1.01/2.4B.P$76 (VSS_PAD), P1.01/2.4B.P$77 (VSS_PAD), P1.01/2.4B.P$78 (VSS_PAD), P1.01/2.4B.P$79 (VSS_PAD), P1.01/2.4B.P$80 (VSS_PAD), P1.01/2.4B.P$81 (VSS_PAD), P1.01/2.4B.P$82 (VSS_PAD), P1.01/2.4B.P$83 (VSS_PAD), P1.01/2.4B.P$84 (VSS_PAD), P1.01/2.4B.P$85 (VSS_PAD), P1.01/2.4B.P$86 (VSS_PAD), P1.01/2.4B.P$87 (VSS_PAD), P1.01/2.4B.P$88 (VSS_PAD), P1.01/2.4B.P$89 (VSS_PAD), P1.01/2.4B.P$90 (VSS_PAD), P1.01/2.4B.P$B7 (VSS), P1.01/2.4B.P$F23 (VSS_PA), R8.2, R9.1, TP_SDA6.TP, X1.2, X1.4; also elsewhere on the board
HAPTIC_EN: P1.01/2.4B.P$U1 (P0.12); also elsewhere on the board
IMU_INT1: IC3.5 (INT1), P1.01/2.4B.P$N1 (P0.08)
IMU_INT2: IC3.6 (INT2), P1.01/2.4B.P$P2 (P1.08)
LX1: IC2.B2 (SW1_1), IC2.B3 (SW1_2), L1.1
LX2: IC2.D2 (SW2_1), IC2.D3 (SW2_2), L1.2
MOSI: P1.01/2.4B.P$B13 (P0.03/AIN1); also elsewhere on the board
unnamed: IC1.D1 (TS/MR), R9.2
unnamed: C9.1, P1.01/2.4B.P$N24 (DEC5)
unnamed: CC3.2, LL1.1, P1.01/2.4B.P$H23 (ANT)
unnamed: IC2.D1 (SCL), R2.2
unnamed: IC2.E1 (SDA), R3.2
unnamed: C20.2, P1.01/2.4B.P$AC5 (DEC3V3)
unnamed 24: ANT1.1 (FEED), CC4.2, CC22.2, LL1.2; also elsewhere on the board
unnamed: CC1.1, P1.01/2.4B.P$B24 (XC1), X1.1
unnamed: CC2.1, P1.01/2.4B.P$A23 (XC2), X1.3
unnamed: CC11.1, P1.01/2.4B.P$D23 (DEC3)
unnamed: C18.1, P1.01/2.4B.P$F2 (P0.01/XL2), X2.1
unnamed: C12.1, P1.01/2.4B.P$A22 (VDD)
unnamed: C13.1, P1.01/2.4B.P$A18 (DEC2)
unnamed: LL2.1, LL3.2
unnamed: LL2.2, P1.01/2.4B.P$B3 (DCC)
unnamed: C15.1, C16.1, CC10.1, LL3.1, P1.01/2.4B.P$B5 (DEC4), P1.01/2.4B.P$E24 (DEC6)
unnamed: C17.1, P1.01/2.4B.P$D2 (P0.00/XL1), X2.2
unnamed: IC3.1 (SDO), R8.1
unnamed: CC5.2, P1.01/2.4B.P$C1 (DEC1)
P0.04: P1.01/2.4B.P$J1 (P0.04/AIN2)
P0.09: P1.01/2.4B.P$L24 (P0.09/NFC1)
P0.13: P1.01/2.4B.P$AD8 (P0.13); also elsewhere on the board
P0.14: P1.01/2.4B.P$AC9 (P0.14); also elsewhere on the board
P0.19: P1.01/2.4B.P$AC15 (P0.19)
P0.20: P1.01/2.4B.P$AD16 (P0.20)
P0.21: P1.01/2.4B.P$AC17 (P0.21)
P0.22: P1.01/2.4B.P$AD18 (P0.22)
P0.23: P1.01/2.4B.P$AC19 (P0.23)
P0.24: P1.01/2.4B.P$AD20 (P0.24)
P0.25: P1.01/2.4B.P$AC21 (P0.25)
P0.26: P1.01/2.4B.P$G1 (P0.26)
P0.27: P1.01/2.4B.P$H2 (P0.27)
P0.28: P1.01/2.4B.P$B11 (P0.28/AIN4)
P0.29: P1.01/2.4B.P$A10 (P0.29/AIN5)
P0.30: P1.01/2.4B.P$B9 (P0.30/AIN6)
P0.31: P1.01/2.4B.P$A8 (P0.31/AIN7)
P1.01: P1.01/2.4B.P$Y23 (P1.01); also elsewhere on the board
P1.02: P1.01/2.4B.P$W24 (P1.02); also elsewhere on the board
P1.03: P1.01/2.4B.P$V23 (P1.03)
P1.04: P1.01/2.4B.P$U24 (P1.04)
P1.05: P1.01/2.4B.P$T23 (P1.05)
P1.06: P1.01/2.4B.P$R24 (P1.06)
P1.07: P1.01/2.4B.P$P23 (P1.07)
P1.09: P1.01/2.4B.P$R1 (P1.09)
P1.10: P1.01/2.4B.P$A20 (P1.10)
P1.11: P1.01/2.4B.P$B19 (P1.11)
P1.12: P1.01/2.4B.P$B17 (P1.12)
P1.13: P1.01/2.4B.P$A16 (P1.13)
P1.14: P1.01/2.4B.P$B15 (P1.14)
P1.15: P1.01/2.4B.P$A14 (P1.15)
PMIC_INT: IC1.A1 (!INT), P1.01/2.4B.P$T2 (P0.11)
RESET: J1.6, P1.01/2.4B.P$AC13 (P0.18/RESET), TP_SDA4.TP; also elsewhere on the board
SCK: P1.01/2.4B.P$A12 (P0.02/AIN0); also elsewhere on the board
SWDCLK: J1.4, P1.01/2.4B.P$AA24 (SWDCLK), TP_SDA3.TP; also elsewhere on the board
SWDIO: J1.2, P1.01/2.4B.P$AC24 (SWDIO), TP_SDA2.TP; also elsewhere on the board
SWO: P1.01/2.4B.P$AD22 (P1.00), TP_SDA1.TP; also elsewhere on the board
VREG: C23.2, C24.2, C39.1, IC1.B2 (SYS), IC2.A1 (EN), IC2.A2 (VIN_1), IC2.A3 (VIN_2), TP_VREG.TP

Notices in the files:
parts and their libraries:
COPYRIGHT: Copyright (C) 2024 Ultra Librarian. All rights reserved.
COPYRIGHT: Copyright (C) 2025 Ultra Librarian. All rights reserved.
